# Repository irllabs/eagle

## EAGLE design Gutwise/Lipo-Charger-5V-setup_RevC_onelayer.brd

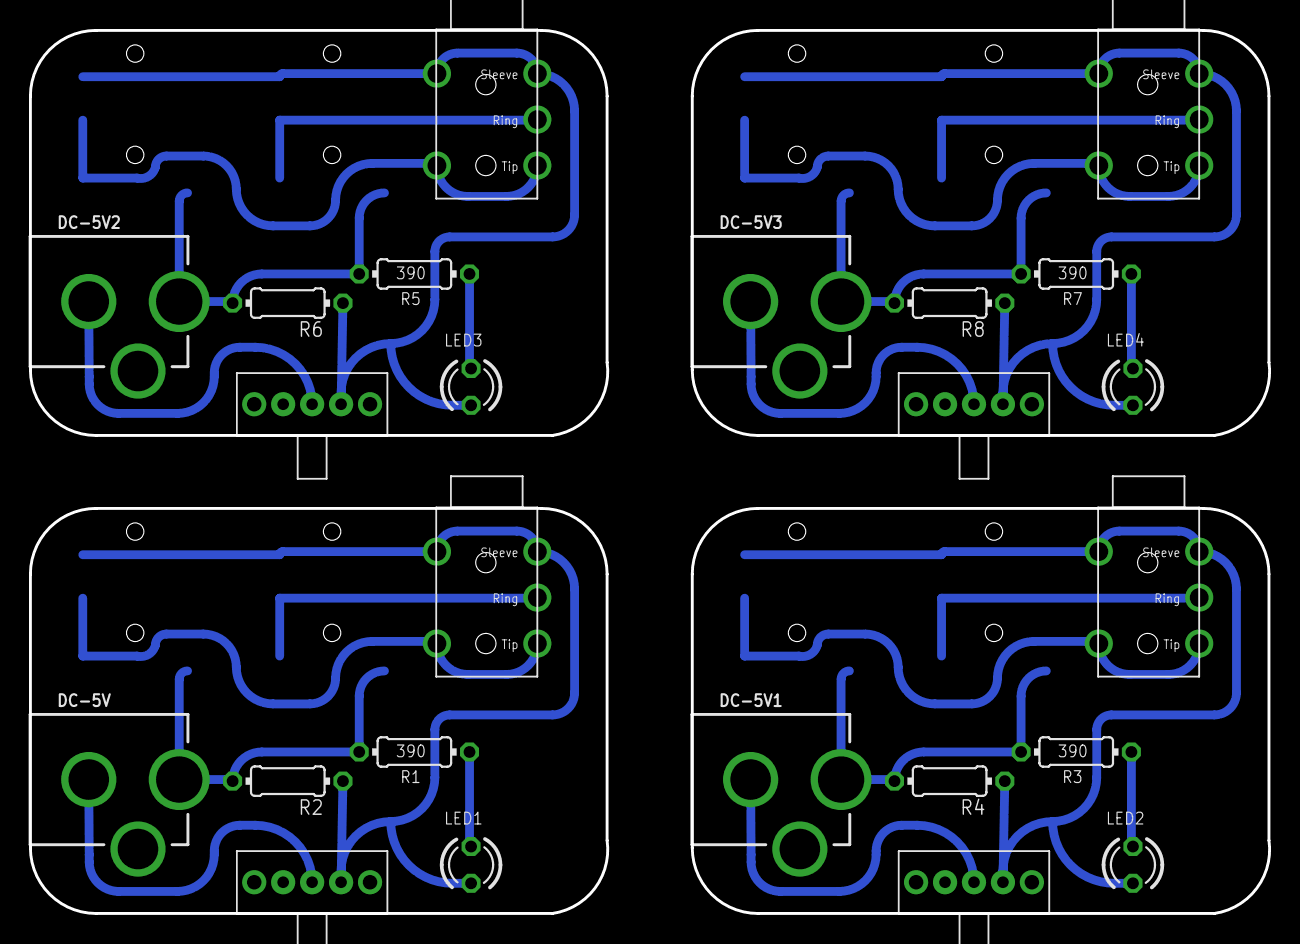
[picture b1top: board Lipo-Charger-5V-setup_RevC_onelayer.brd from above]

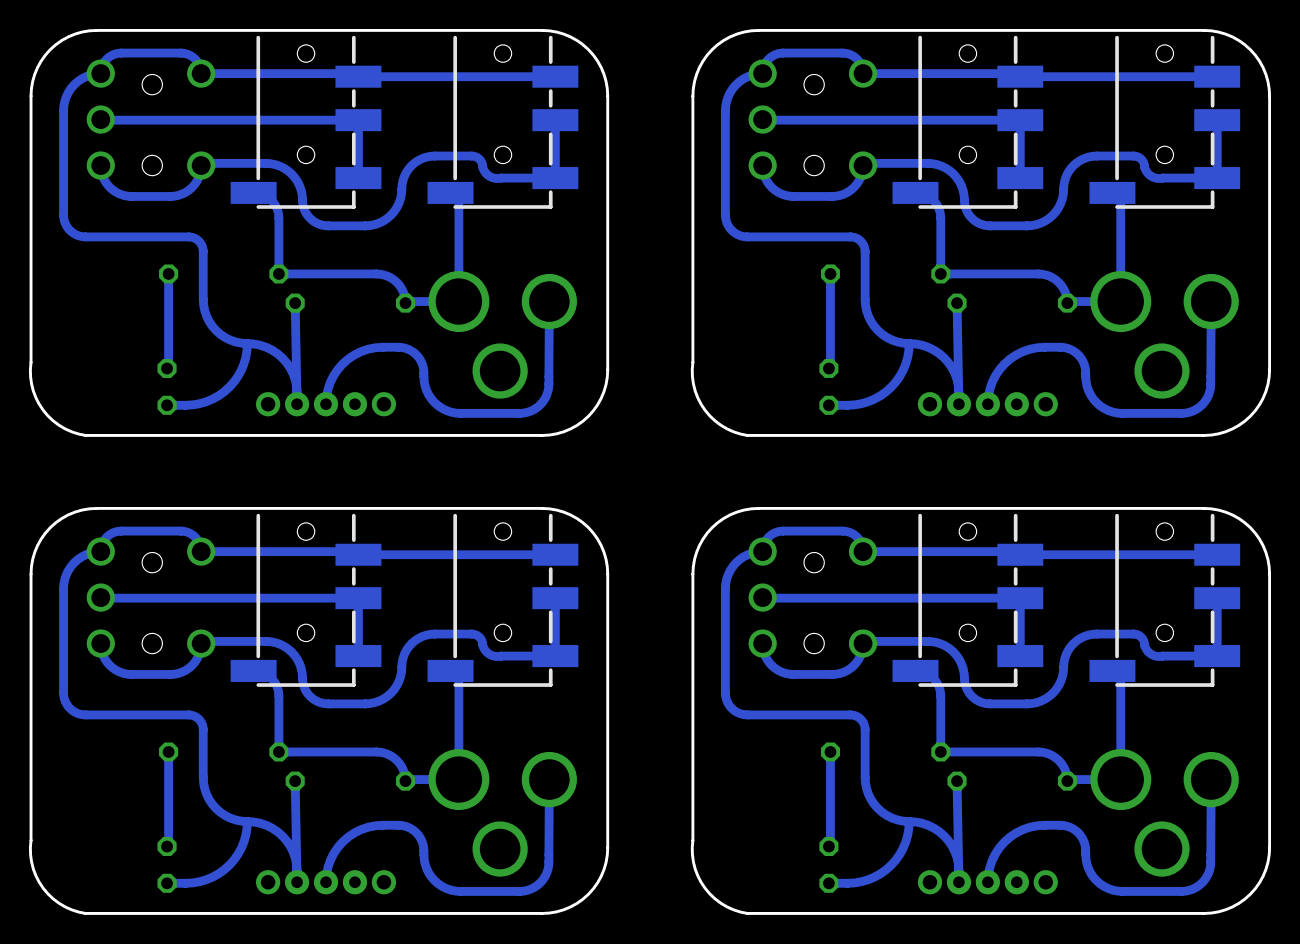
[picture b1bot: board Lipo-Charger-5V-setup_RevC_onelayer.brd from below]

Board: 2 copper layers, 85.6 x 61.0 mm, 32 parts (8 on the bottom side), 24 nets.

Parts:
AUDIO_OUT, AUDIO_OUT1, AUDIO_OUT2, AUDIO_OUT3: 1/8"-F-STEREO-PCB
DC-5V, DC-5V1, DC-5V2, DC-5V3: DCJACK_2MM_PTH
LED1, LED2, LED3, LED4: LED3MM
POWER, POWER1, POWER2, POWER3: SPDT; SWITCH_SPDT-TE-CONNECT
R1, R3, R5, R7: 390; 0204/7
R2, R4, R6, R8: 50; 0204/7
U$1, U$2, U$3, U$4, U$5, U$6, U$7, U$8: AUDIO-JACK3LGPADS; AUDIO-JACK-TRRS-SMD

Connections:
+5V: DC-5V.PWR, R1.2, R2.2, U$4.EARTH, U$5.EARTH
+5V1: DC-5V1.PWR, R3.2, R4.2, U$1.EARTH, U$2.EARTH
+5V2: DC-5V2.PWR, R5.2, R6.2, U$3.EARTH, U$6.EARTH
+5V3: DC-5V3.PWR, R7.2, R8.2, U$7.EARTH, U$8.EARTH
GND: AUDIO_OUT.SLEEVE1, AUDIO_OUT.SLEEVE2, LED1.K, POWER.3, R2.1, U$4.RING2, U$5.RING2
GND1: AUDIO_OUT1.SLEEVE1, AUDIO_OUT1.SLEEVE2, LED2.K, POWER1.3, R4.1, U$1.RING2, U$2.RING2
GND2: AUDIO_OUT2.SLEEVE1, AUDIO_OUT2.SLEEVE2, LED3.K, POWER2.3, R6.1, U$3.RING2, U$6.RING2
GND3: AUDIO_OUT3.SLEEVE1, AUDIO_OUT3.SLEEVE2, LED4.K, POWER3.3, R8.1, U$7.RING2, U$8.RING2
unnamed: LED2.A, R3.1
unnamed: LED1.A, R1.1
unnamed: AUDIO_OUT1.RING, U$2.RING1, U$2.TIP
unnamed: DC-5V.GND, POWER.2
unnamed: DC-5V1.GND, POWER1.2
unnamed: LED3.A, R5.1
unnamed: AUDIO_OUT2.RING, U$6.RING1, U$6.TIP
unnamed: AUDIO_OUT.RING, U$5.RING1, U$5.TIP
unnamed: DC-5V2.GND, POWER2.2
unnamed: LED4.A, R7.1
unnamed: AUDIO_OUT3.RING, U$8.RING1, U$8.TIP
unnamed: DC-5V3.GND, POWER3.2
OUT1: AUDIO_OUT1.TIP1, AUDIO_OUT1.TIP2, U$1.RING1, U$1.TIP
OUT2: AUDIO_OUT.TIP1, AUDIO_OUT.TIP2, U$4.RING1, U$4.TIP
OUT3: AUDIO_OUT2.TIP1, AUDIO_OUT2.TIP2, U$3.RING1, U$3.TIP
OUT4: AUDIO_OUT3.TIP1, AUDIO_OUT3.TIP2, U$7.RING1, U$7.TIP

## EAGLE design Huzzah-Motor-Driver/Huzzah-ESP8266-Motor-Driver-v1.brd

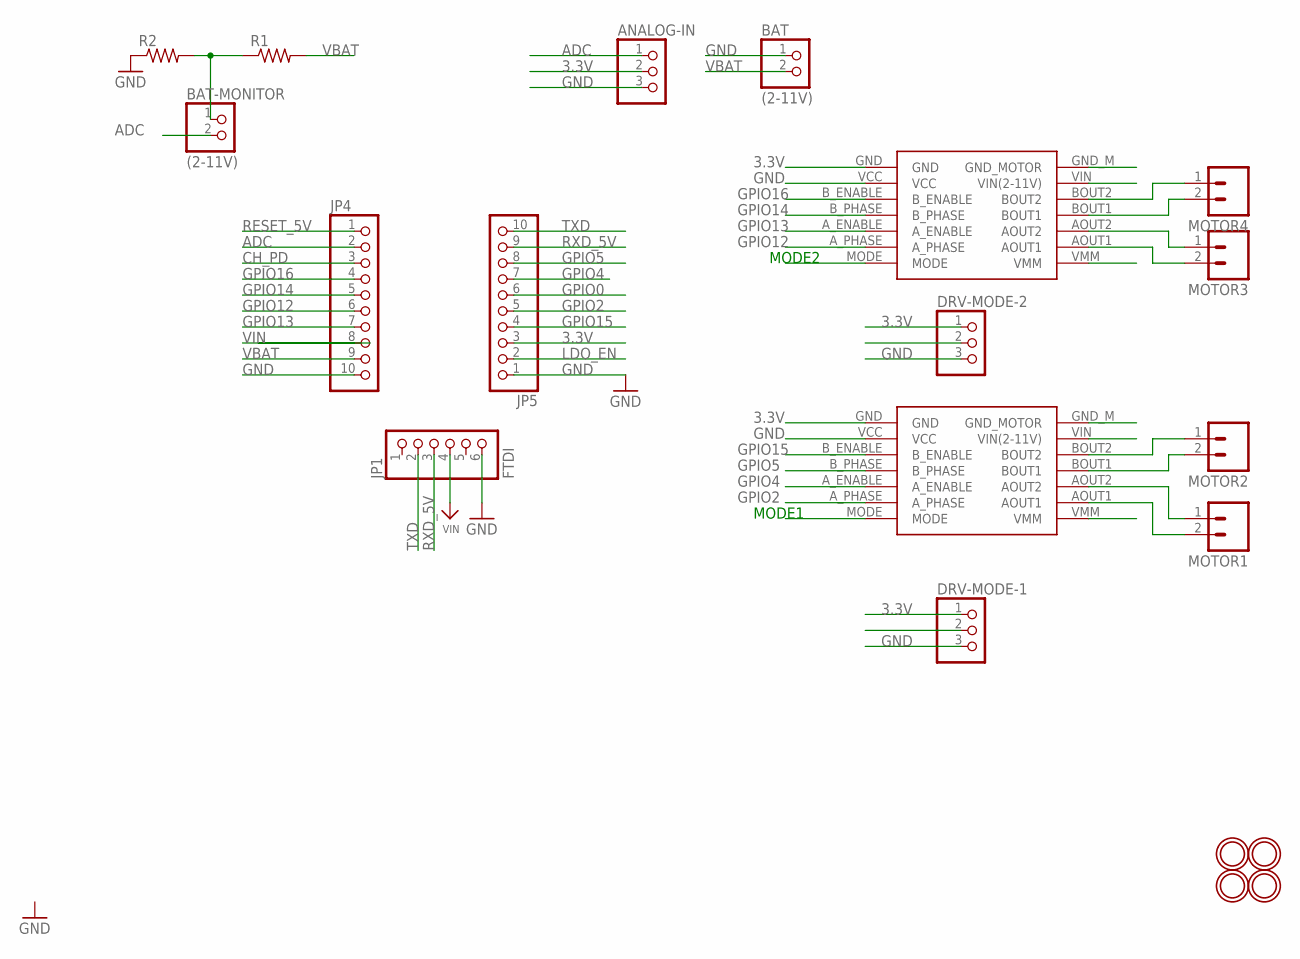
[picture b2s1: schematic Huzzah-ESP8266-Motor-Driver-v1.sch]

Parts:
ANALOG-IN: PINHD-1X3; 1X03
BAT: (2-11V); 1X02
BAT-MONITOR: (2-11V); 1X02
DRV8835-1, DRV8835-2: POLOLU_DRV8835
DRV-MODE-1, DRV-MODE-2: PINHD-1X3; 1X03
JP1: FTDI; 1X06_ROUND_70
JP4, JP5: HEADER-1X1070MIL; 1X10_ROUND70
MOTOR1, MOTOR2, MOTOR3, MOTOR4: M02SPRING-2.54-RA; SPRINGTERMINAL-2.54MM-2
R1, R2: R-US_0204/5; 0204/5
U$15, U$16, U$17, U$18: MOUNTINGHOLE2.5; MOUNTINGHOLE_2.5_PLATED

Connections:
3.3V: ANALOG-IN.2, DRV8835-1.VCC, DRV8835-2.VCC, DRV-MODE-1.1, DRV-MODE-2.1, JP5.3
ADC: ANALOG-IN.1, BAT-MONITOR.2, JP4.2
CH_PD: JP4.3
GND: ANALOG-IN.3, BAT.1, DRV8835-1.GND, DRV8835-1.GND_M (GND_MOTOR), DRV8835-2.GND, DRV8835-2.GND_M (GND_MOTOR), DRV-MODE-1.3, DRV-MODE-2.3, JP1.6, JP4.10, JP5.1, R2.1
GPIO0: JP5.6
GPIO2: JP5.5
GPIO4: JP5.7
GPIO5: JP5.8
GPIO12: JP4.6
GPIO13: JP4.7
GPIO14: JP4.5
GPIO15: JP5.4
GPIO16: JP4.4
LDO_EN: JP5.2
MODE1: DRV8835-1.MODE
MODE2: DRV8835-2.MODE
unnamed: DRV8835-1.AOUT1, MOTOR1.2
unnamed: DRV8835-1.AOUT2, MOTOR1.1
unnamed: DRV8835-1.BOUT1, MOTOR2.2
unnamed: DRV8835-1.BOUT2, MOTOR2.1
unnamed: DRV8835-2.AOUT1, MOTOR3.2
unnamed: DRV8835-2.AOUT2, MOTOR3.1
unnamed: DRV8835-2.BOUT2, MOTOR4.1
unnamed: DRV8835-2.BOUT1, MOTOR4.2
unnamed: BAT-MONITOR.1, R1.1, R2.2
RESET_5V: JP4.1
RXD_5V: JP1.3, JP5.9
TXD: JP1.2, JP5.10
VBAT: BAT.2, DRV8835-1.VIN (VIN(2-11V)), DRV8835-2.VIN (VIN(2-11V)), JP4.9, R1.2
VIN: JP1.4, JP4.8

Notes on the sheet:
MODE1
MODE2

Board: 2 copper layers, 23 parts (3 on the bottom side), 16 nets, no tracks yet.

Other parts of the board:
U$2: HUZZAHLOGO
U$12: ADAFRUIT_TEXT_20MM
U$13: PCBFEAT-REV-040

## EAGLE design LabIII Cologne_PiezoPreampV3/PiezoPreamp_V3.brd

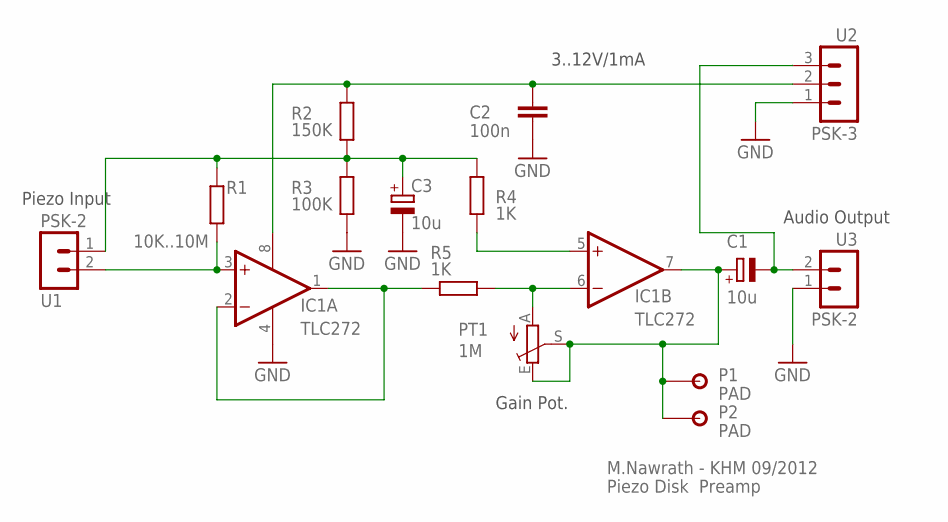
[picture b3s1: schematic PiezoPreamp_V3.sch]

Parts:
C1, C3: 10u; E2,5-5
C2: 100n; C025-025X050
IC1: TLC272; DIL08
P1, P2: PAD; PAD127L1
PT1: 1M; CA6V
R1: 10K..10M; 0204/5
R2: 150K; 0204/5
R3: 100K; 0204/5
R4, R5: 1K; 0204/5
U1, U3: PSK-2; PSK254/2
U2: PSK-3; PSK254/3

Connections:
GND: C2.1, C3.-, IC1.4 (V-), R3.1, U2.1, U3.1
unnamed: IC1.6 (-IN), PT1.A, R5.1
unnamed: C1.-, U2.3, U3.2
unnamed: IC1.5 (+IN), R4.1
unnamed: C1.+, IC1.7 (OUT), P1.P$2, P2.P$2, PT1.E, PT1.S
unnamed: IC1.1 (OUT), IC1.2 (-IN), R5.2
unnamed: IC1.3 (+IN), R1.1, U1.2
unnamed: C3.+, R1.2, R2.2, R3.2, R4.2, U1.1
V9V: C2.2, IC1.8 (V+), R2.1, U2.2

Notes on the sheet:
Piezo Disk Preamp
M.Nawrath - KHM 09/2012
Audio Output
Piezo Input
3..12V/1mA
Gain Pot.

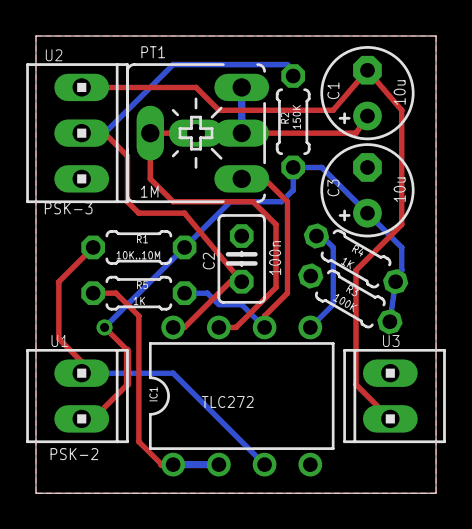
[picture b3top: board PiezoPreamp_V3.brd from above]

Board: 2 copper layers, 22.2 x 25.4 mm, 15 parts (0 on the bottom side), 9 nets.

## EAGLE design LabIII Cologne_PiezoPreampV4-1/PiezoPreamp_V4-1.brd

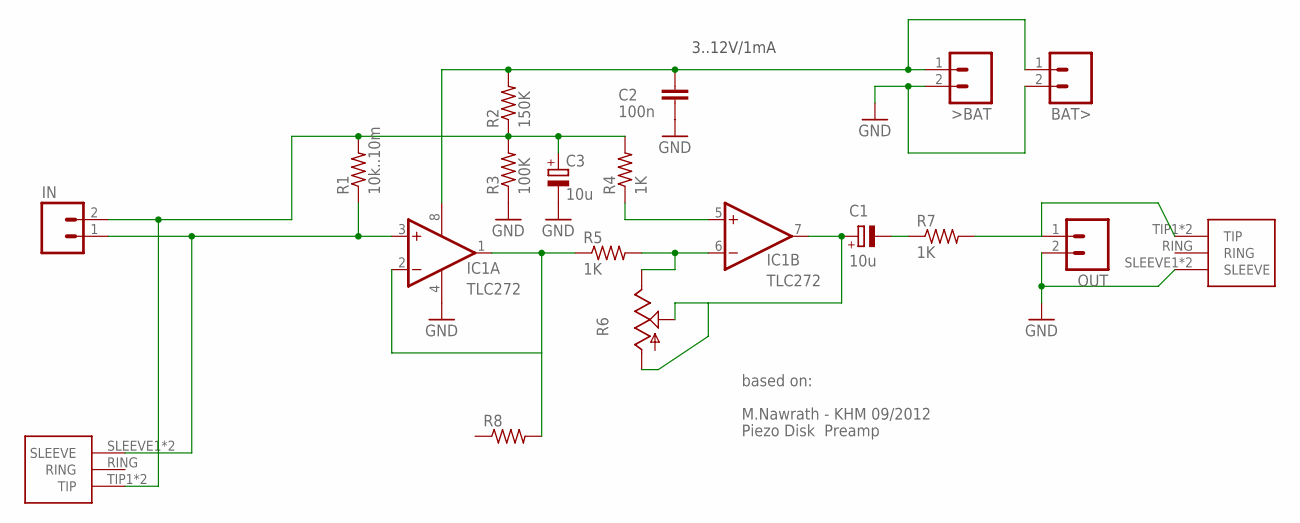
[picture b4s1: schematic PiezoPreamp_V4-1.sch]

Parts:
>BAT: M02LOCK; 1X02_LOCK
BAT>: M02LOCK; 1X02_LOCK
C1, C3: 10u; E2,5-5
C2: 100n; C025-025X050
IC1: TLC272; DIL08
IN: M02LOCK; 1X02_LOCK
OUT: M02LOCK; 1X02_LOCK
OUT1-TRS: 1/8"-F-STEREO-PCB
R1: 10k..10m; 0204V
R2: 150K; 0204V
R3: 100K; 0204V
R4, R5, R7: 1K; 0204V
R6: TRIM_US-CA6V; CA6V
R8: R-US_0613/5V; P0613V
U$2: 1/8"-F-STEREO-PCB

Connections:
GND: >BAT.2, BAT>.2, C2.1, C3.-, IC1.4 (V-), OUT.2, OUT1-TRS.SLEEVE1 (SLEEVE), OUT1-TRS.SLEEVE2 (SLEEVE), R3.1
unnamed: C3.+, IN.2, R1.2, R2.1, R3.2, R4.2, U$2.TIP1 (TIP), U$2.TIP2 (TIP)
unnamed: IC1.6 (-IN), R5.2, R6.E
unnamed: OUT.1, OUT1-TRS.TIP1 (TIP), OUT1-TRS.TIP2 (TIP), R7.2
unnamed: C1.-, R7.1
unnamed: IC1.5 (+IN), R4.1
unnamed: C1.+, IC1.7 (OUT), R6.A, R6.S
unnamed: IC1.3 (+IN), IN.1, R1.1, U$2.SLEEVE1 (SLEEVE), U$2.SLEEVE2 (SLEEVE)
unnamed: IC1.1 (OUT), IC1.2 (-IN), R5.1, R8.2
V9V: >BAT.1, BAT>.1, C2.2, IC1.8 (V+), R2.2

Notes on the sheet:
Piezo Disk Preamp
M.Nawrath - KHM 09/2012
3..12V/1mA
based on:

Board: 2 copper layers, 18 parts (0 on the bottom side), 10 nets, no tracks yet.

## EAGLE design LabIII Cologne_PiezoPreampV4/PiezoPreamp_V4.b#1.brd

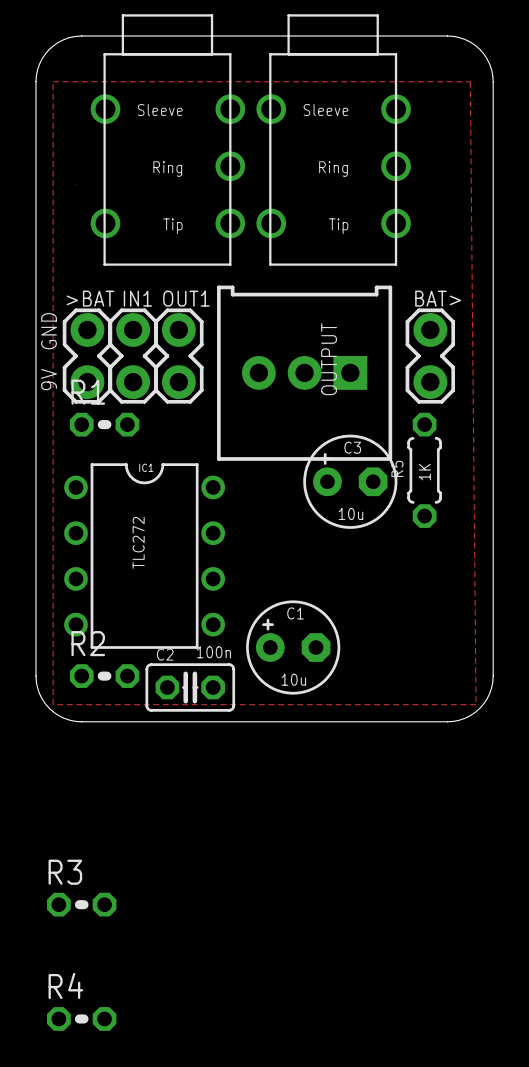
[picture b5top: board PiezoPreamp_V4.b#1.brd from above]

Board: 2 copper layers, 25.4 x 38.1 mm, 16 parts (0 on the bottom side), 9 nets, no tracks yet.

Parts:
>BAT: 1X02_LOCK
BAT>: 1X02_LOCK
C1, C3: 10u; E2,5-5
C2: 100n; C025-025X050
IC1: TLC272; DIL08
IN1: 1X02_LOCK
OUT1: 1X02_LOCK
OUT1-TRS: 1/8"-F-STEREO-PCB
R1: 10k..10m; 0204V
R2: 150K; 0204V
R3: 100K; 0204V
R4: 1K; 0204V
R5: 1K; 0204/5
R6: Gain-pot 10M; 3386U
U$2: 1/8"-F-STEREO-PCB

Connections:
GND: >BAT.2, BAT>.2, C2.1, C3.-, IC1.4, OUT1.2, OUT1-TRS.SLEEVE1, OUT1-TRS.SLEEVE2, R3.1
unnamed: C3.+, IN1.2, R1.2, R2.1, R3.2, R4.2, U$2.TIP1, U$2.TIP2
unnamed: IC1.6, R5.1, R6.1
unnamed: C1.-, OUT1.1, OUT1-TRS.TIP1, OUT1-TRS.TIP2
unnamed: IC1.5, R4.1
unnamed: C1.+, IC1.7, R6.2, R6.3
unnamed: IC1.3, IN1.1, R1.1, U$2.SLEEVE1, U$2.SLEEVE2
unnamed: IC1.1, IC1.2, R5.2
V9V: >BAT.1, BAT>.1, C2.2, IC1.8, R2.2

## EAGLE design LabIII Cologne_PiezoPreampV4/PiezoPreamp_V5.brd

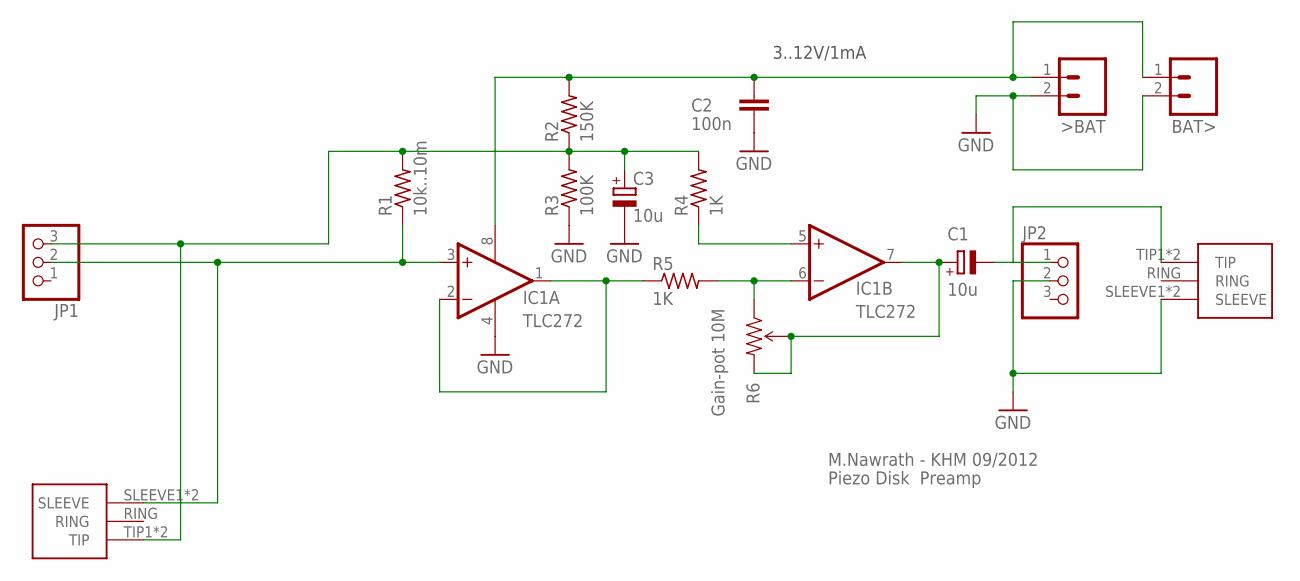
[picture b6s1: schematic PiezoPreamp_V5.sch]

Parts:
>BAT: M02LOCK; 1X02_LOCK
BAT>: M02LOCK; 1X02_LOCK
C1, C3: 10u; E2,5-5
C2: 100n; C025-025X050
IC1: TLC272; DIL08
JP1, JP2: PINHD-1X3; 1X03
OUT1-TRS: 1/8"-F-STEREO-PCB
R1: 10k..10m; 0204V
R2: 150K; 0204V
R3: 100K; 0204V
R4, R5: 1K; 0204V
R6: Gain-pot 10M; 3386U
U$2: 1/8"-F-STEREO-PCB

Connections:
GND: >BAT.2, BAT>.2, C2.1, C3.-, IC1.4 (V-), JP2.2, OUT1-TRS.SLEEVE1 (SLEEVE), OUT1-TRS.SLEEVE2 (SLEEVE), R3.1
unnamed: C3.+, JP1.3, R1.2, R2.1, R3.2, R4.2, U$2.TIP1 (TIP), U$2.TIP2 (TIP)
unnamed: IC1.6 (-IN), R5.2, R6.1 (CCW)
unnamed: IC1.5 (+IN), R4.1
unnamed: C1.+, IC1.7 (OUT), R6.2 (WIPER), R6.3 (CW)
unnamed: IC1.3 (+IN), JP1.2, R1.1, U$2.SLEEVE1 (SLEEVE), U$2.SLEEVE2 (SLEEVE)
unnamed: IC1.1 (OUT), IC1.2 (-IN), R5.1
OUT1: C1.-, JP2.1, OUT1-TRS.TIP1 (TIP), OUT1-TRS.TIP2 (TIP)
V9V: >BAT.1, BAT>.1, C2.2, IC1.8 (V+), R2.2

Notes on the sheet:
Piezo Disk Preamp
M.Nawrath - KHM 09/2012
3..12V/1mA

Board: 2 copper layers, 16 parts (0 on the bottom side), 9 nets, no tracks yet.

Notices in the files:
parts and their libraries:
microbuilder: This work is placed in the public domain, and may be freely used for commercial and non-commercial work with the following conditions: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
SparkFun-Connectors: Licensing: Creative Commons ShareAlike 4.0 International - https://creativecommons.org/licenses/by-sa/4.0
